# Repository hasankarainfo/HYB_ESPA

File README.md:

# HYB_ESPA CNC CONTROLLER BOARD
4 Adet Step motor bağlanabilir CNC kontrol kartı.

<p align="center"> Tasarım Ön Görünüm</p>

<p align="center"> Tasarım Arka Görünüm </p>

### ESP32 ile tasarlanmış cnc kontrolcü kartlarına genel bakış;

Temelde donanımsal olarak iki farklı yapıda görmek mümkün. 
İlki daha sade olan (ESPA), doğrudan mcu pinleri ile çevresel bileşen bağlantılandırılmış. 
İkincisi ise (ESPE), bazı bileşenlerin çıkış gpio ihtiyaçları için hc595 entegreleri kullanılıyor olması.

FYSETC_E4, Hem marlin hem fluidnc hem grbl firmware yazılımlarıyla uyumlu hemde açık kaynak paylaşılan projeden şematik olarak faydalanmak mümkün.
Altium ile geliştirilen proje açık kaynak paylaşılmıştır. 4 Adet TMC2209 dahili olarak step sürücüleri üzerinde barındırıyor. 
Sürücü uart bağlantıları ve uart donanımsal adreslemesini kullanmaktadır.

MKS-TinyBee, firmware yazılımları ile yine fazlaca uyumlu, yalnız kaynak tasarım olarak açık da yalnızca pdf bulunuyor. GPIO genişleme yapısı kullanılıyor. 
5 adet motor sürücü için 2* dip-8 header standart pololu breakout yapısı kullanılarak esnek motor sürücü bağlantı seçeneği sunmakta. 
yalnız TMC2208 ve ..09 için uart bağlantısı göz ardı edilmiş. Step sürücü header pinlerindeki RST ve SLP pinleri doğrudan kısa devre edili olmaktadır.

MRR_ESPE kicad ile tasarlanmış ve açık kaynak olarak paylaşılmış, tinybee ile yapısal olarak ve mcu pin görevleri olarak fazlaca benzerliği bulunan bir proje.
ek olarak SPI uyumlu step sürücüler ile haberleşmeli kullanılabilmesi için jumper seçenekleri sunmakta. 

Step sürücü header pinlerindeki MS1, MS2, MS3, RST jumper ile kontrol edilebilirken RST ve SLP pinleri de hem jumper ile kısa devre yapılaibliyor hemde kısa devre kaldırılıp mcu ya bağlanabiliyor. Özellikle TMC2208 ve ..09 uart haberleşmesi için MS3->TX ve SLP->RX olarak kullanılabileceği için gerekli esneklikler sağlanmış olmakta. 

MRR_ESPA ise yine açık kaynak paylaşılmış gpio genişleme kullanılmayan versiyonu olarak düşünülebilir.

Uart haberleşmeli step motor sürücüleri, çoğu kontrolcüye etkili düzeyde avantaj sağlamaktadır. 
Her sürücü Uart haberleşmesi için ayrıca mcu ya bağlamak fazlaca gpio kullanımı gerektirebilir.
ESP32 nin kısıtlı pin durumu için bu bir problem haline gelir. Bu sebeple Tek bir sürücüyü hem rx hem tx ile mcu bağlayıp, tüm sürücülerin sadece rx pinlerini paralel bağlamak kısmen çözüm olabiliyor.

Toplamda 2 pin gpio kullanılarak tüm sürücülere komut gönderimi mümkün olabiliyor, özellikle mod geçişleri, eşik değerleri, akım limiti microstep gibi değerlerin güncellenmesi mümkün olur.
TMC2209 uart adresleme özelliği bulunur iken TMC2208 bu özelliği desteklemez ve adres farketmeksizin tüm komutlara geri bildirim göndermektedir.
TMC2209 step motor limit switch özelliği barındırır, TMC2208 bu özellik yine bulunmamaktadır.
TMC2209 Uart adreslemesi için MS1 ve MS2 pinlerini kullanır, farklı adreslenerek uart bağlantısı paralellenmiş TMC2209 sürücüleri ile birebir haberleşme mümkün olur. 

Tek uart bağlantısı ile çoklu TMC2208 haberleşmesi kısmen mümkün olabilmektedir. Sürücülerin hepsi rx özelliği aktif iken, yalnızca birisi tx yapabilecek donanım yapısı kurgulandığında tüm sürücülere aynı parametre yükleme başarılı olmaktadır.

Açık kaynak paylaşımlar incelendiğinde esnek ve sade yapısı ile FYSETC_E4 projesi dikkat çekmektedir. 

Kendi tasarımımızı şekillendirirken özellikle gpio numara görev atamalarında ve step motor sürücü sayısında FYSETC_E4 esinlenmiş olduk.

### Tasarıma ilişkin;
1. Step motor sürücüleri pololu breakout pin yapısına uyumlu tasarlanarak, farklı step motor sürücülerine uyumluluk sağlandı. 
2. TMC2208 sürücüleri ile kullanıldığında uart üzerinden parametre yüklenebilir iken, TMC2209 ile UART RX-TX jumper takılarak, ve sürücülerde MS1, MS2 jumper configurasyonu ile uart adreslemeli kullanılabilirlik sağlandı.
3. +24V giriş voltajı ve P-mos yapısında ters bağlantı koruma özelliği eklendi.
4. Air out çıkışı ile, 42A akım değerinde ki P-mos ile Denetleyiciden kontrol edilen güçlü bir çıkış elde edildi. 24V ile beslenen lazer yada spindle doğrudan bu terminalden beslenebilir.
5. Emergency Switch terminal ile, step motor beslemesi ve Air out çıkışı, kontrolcüden bağımsız olarak kesilebilir. Kontrolcü beslemesi ve 5V hattı enerjisi aktif devam eder.
6. 5V fan çıkışı, USB ve LimitSwitch enerji hatları bağımsız PTC sigortaları ile akım korumaları eklendi.
7. Limit switch girişleri x,y ve z eksenleri için çiftlendi, aynı eksene iki farklı limit switch eklenebilir. Limit switch bağlantısı koparsa algılayabilir. Kullanılmayan giriş gnd jumper bağlanmalıdır.
8. Boot için kullanılan gpio 0 Probe bağlantısı için de kullanılmaya başlandı. ESP32 e kod atmak için Probe pini 5v jumperda iken kart resetlenerek başlatılmalıdır.
9. Tasarım aracı olarak Kicad 9 kullanıldı.

###  Layout tarafında;
1. Arduino mega2560 fiziksel boyutlarından esinlenerek 60x100 mm^2 ile alternatif cnc kontrolcü kartlarına kıyasla daha küçük ve sade yapıda tasarlandı.
2. Çift yüz tasarım yapılırken, yalnız 0.8mm delikli vialar kullanıldı. THT komponentler yalnızca arka katmandan bağlantılandı. 
3. Komponentlerin altında via bırakılmayarak kendin yap pcb üretim teknikleri ile üretim mümkün kılındı.
4. 40x40 fan doğrudan pcb üzerine distanslar ile sabitlenebilecek şekilde M3 vida delikleri yerleştirildi.

### ÜRETİM
Profesyonel pcb üretimi için; Plot klasörü içerisinde gerber ve drill dosyaları oluşturuldu.

Kendin yap seçeneği ile pcb üretimi için;
1. Plot_DIY klasörü içerisinde pcb delim için 0.8, 0.9, 1.2, 1.4, 3 mm kalınlıklarında matkap uçlarında farklı gcode lar oluşturuldu.
2. PCB komponent lehimleme işlemi için, F_Paste lazer kesim dosyası ayrıca oluşturuldu. Standart etiket kağıdına kesim yapılabilmektedir.
3. Ön yüz ve Arka yüz lazer kazıma ve hizalaması için gerekli dosyalar oluşturuldu.
4. ESP32 montajlanırken kullanılmayan pinler kapton bant ile izolasyon sağlanmalıdır.
5. ibom klasörü içerisinde html uzantılı web browser da görüntülemek üzere bom dosyası oluşturuldu. Komponent yerleşim ve dizgisinde kullanılabilmektedir.
6. Tüm lazer cnc üretim dosyaları 30W optik gücünde ki lazer makinasına göre kurgulanmıştır. Güç oranlaması ile farklı güçte ki lazer makinalarına uygunlaştırılabilir.

### 0.1b versiyon kendin yap teknikleri ile üretilmiş prototiplere ilişkin görseller

<p align="center">SMD Dizgili Ön ve Arka Görünüm </p>

<p align="center">Tam Dizgili ve Makine Montajlanmış Görünüm </p>

İlk prototipleme ile birlikte küçük çaplı düzeltmeler tasarımda ve üretim dosyalarında güncellenmiş (v0.1) haldedir.

Bom list oluşturulurken Türkiye piyasasından temin edilmek üzere ürün linkleri oluşturuldu. Yalnız CH340E IC yerli piyasada bulunamadı. 
Belirtilen fiyat bilgileri için ise, vergiler dahil edildi, güncel dolar kuru esas alındı ve dolara çevrildi.

### Bazı testlere ilişkin;
1. Firmware olarak fluidnc v3.9.4 yüklendi. Kontrolcüyle uyumlu, oluşturulan config.yaml dosyası "Settings/" dizini içerisine yerleştirildi.
2. X, Y ve Z eksenleri için 3 adet TMC2208 step motor sürücüleri bağlandı. Tüm sürücülere parametre yükleme yapılabildiği teyit edildi.
3. Arayüz olarak UGS (version 2.1.12) ile bağlanarak temel testler başarıyla sağlandı. 
4. Fiziksel SD kart takılarak web arayüz üzerinden .gcode yüklendi ve ilgili gcode çalıştırıldı. 
5. AirOut çıkışına fiziksel röle bağlandı ve röle çıkışına spindle 220V beslemesi bağlandı.
6. Fluidnc config ayarlarında AirOut çıkışı pwm enable pini ile ilişkilendirildi. 
7. M3 komutu çalıştırılarak Spindle enerjisi sağlandı, M5 komutu çalıştırıldığında Spindle enerjisi otomatik kesildi.
8. Pwm çıkışı ile spindle motor hız ayarı çalıştırıldı.
9. Kontrolcü spindle için enerji çıkışı sağlarken de acil stop basıldığında, spindle enerjisi doğrudan kesilebildi.
10. Limit switch kablo temassızlığı algılanabildiği görüldü.

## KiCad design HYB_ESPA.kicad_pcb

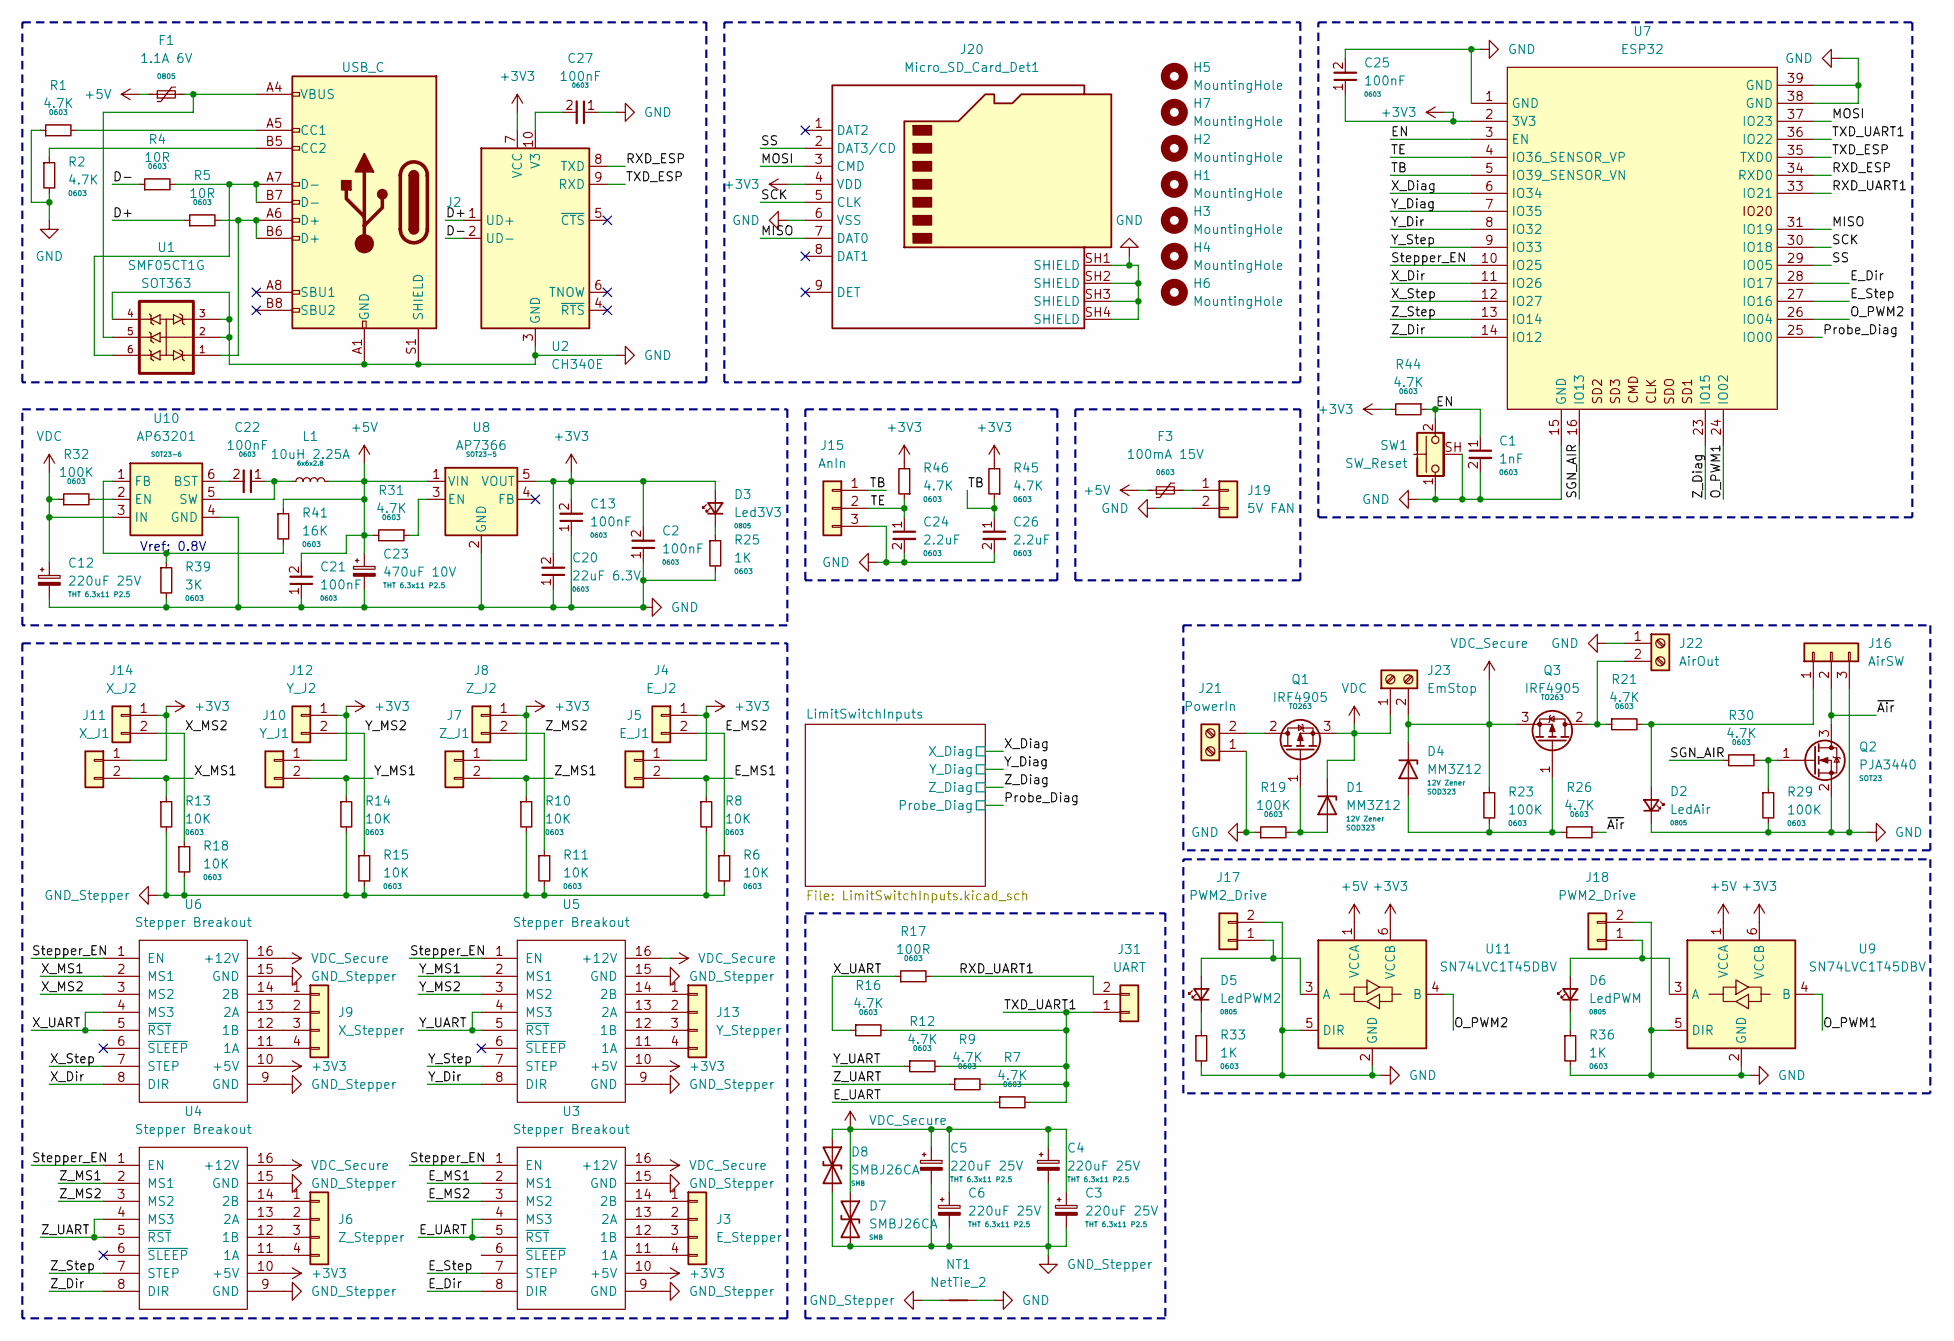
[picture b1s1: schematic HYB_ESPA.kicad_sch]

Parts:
C1: 1nF; C_0603_1608Metric; Part Number CL10B102KB8NNNC
C2, C13, C21, C22, C25, C27: 100nF; C_0603_1608Metric_SlimPad; Part Number CC0603KRX7R9BB104
C3, C4, C5, C6, C12: 220uF 25V; CP_Radial_D6.3mm_H11.0mm_P2.50mm; Part Number TMP221M1EE11M
C20: 22uF 6.3V; C_0603_1608Metric; Part Number CL10A226MQ8NRNC
C23: 470uF 10V; CP_Radial_D6.3mm_H11.0mm_P2.50mm; Part Number PKLH-010V471ME110-T2.5
C24, C26: 2.2uF; C_0603_1608Metric_SlimPad; Part Number CL10A225KQ8NNNC
D1, D4: MM3Z12; D_SOD-323_HandSoldering; Part Number MM3Z12-HT
D2: LedAir; LED_0805_2012Metric-s; Part Number HL-PSC-2012H233W-HF4
D3: Led3V3; LED_0805_2012Metric-s; Part Number HL-PSC-2012H233W-HF4
D5: LedPWM2; LED_0805_2012Metric-s; Part Number HL-PSC-2012H233W-HF4
D6: LedPWM; LED_0805_2012Metric-s; Part Number HL-PSC-2012H233W-HF4
D7, D8: SMBJ26CA; D_SMB_SmallPad; Part Number SMBJ26CA-HT
F1: 1.1A 6V; Fuse_0805_2012Metric; Part Number KLM2S110RY
F3: 100mA 15V; Fuse_0603_1608Metric; Part Number FSMD010-0603-R
H1, H2, H3, H4, H5, H6, H7: MountingHole; MountingHole_3.2mm_M3_DIN965_SmallPad
J2: USB_C; USB_C_Receptacle_GCT_USB4105-xx-A_16P_TopMnt_Horizontal_SPEC; Part Number nc
J3: E_Stepper; JST_XH_B4B-XH-A_1x04_P2.50mm_Vertical; Part Number DS1069-4MVW6X
J4: E_J2; PinHeader_1x02_P2.54mm_Vertical_1L; Part Number DS1069-2MVW6X
J5: E_J1; PinHeader_1x02_P2.54mm_Vertical_1L; Part Number DS1069-2MVW6X
J6: Z_Stepper; JST_XH_B4B-XH-A_1x04_P2.50mm_Vertical; Part Number DS1069-4MVW6X
J7: Z_J1; PinHeader_1x02_P2.54mm_Vertical_1L; Part Number DS1069-2MVW6X
J8: Z_J2; PinHeader_1x02_P2.54mm_Vertical_1L; Part Number DS1069-2MVW6X
J9: X_Stepper; JST_XH_B4B-XH-A_1x04_P2.50mm_Vertical; Part Number DS1069-4MVW6X
J10: Y_J1; PinHeader_1x02_P2.54mm_Vertical_1L; Part Number DS1069-2MVW6X
J11: X_J1; PinHeader_1x02_P2.54mm_Vertical_1L; Part Number DS1069-2MVW6X
J12: Y_J2; PinHeader_1x02_P2.54mm_Vertical_1L; Part Number DS1069-2MVW6X
J13: Y_Stepper; JST_XH_B4B-XH-A_1x04_P2.50mm_Vertical; Part Number DS1069-4MVW6X
J14: X_J2; PinHeader_1x02_P2.54mm_Vertical_1L; Part Number DS1069-2MVW6X
J15: AnIn; JST_XH_B3B-XH-A_1x03_P2.50mm_Vertical; Part Number L-KLS1-2.50-03-S
J16: AirSW; JST_XH_B3B-XH-A_1x03_P2.50mm_Vertical; Part Number L-KLS1-2.50-03-S
J17, J18: PWM2_Drive; JST_XH_B2B-XH-A_1x02_P2.50mm_Vertical; Part Number DS1069-2MVW6X
J19: 5V FAN; JST_XH_B2B-XH-A_1x02_P2.50mm_Vertical; Part Number DS1069-2MVW6X
J20: Micro_SD_Card_Det1; MicroSD_Card_Holder; Part Number 112I-TA01
J21: PowerIn; PhoenixContact_MSTBVA_2,5_2-G-5,08_1x02_P5.08mm_Vertical; Part Number ZB2EDGV-5.08-2P
J22: AirOut; TerminalBlock_Phoenix_PT-1,5-2-3.5-H_1x02_P3.50mm_Horizontal; Part Number 15EDGVC-3.5-02P-12-00AH
J23: EmStop; PhoenixContact_MSTBVA_2,5_2-G-5,08_1x02_P5.08mm_Vertical; Part Number ZB2EDGV-5.08-2P
J31: UART; PinHeader_1x02_P2.54mm_Vertical_1L; Part Number DS1069-2MVW6X
L1: 10uH 2.25A; L_CoreMaster_NR6028; Part Number NR6028-100M
NT1: NetTie_2; NetTie-2_SMD_Pad2.0mm
Q1, Q3: IRF4905; TO-263-2-S; Part Number IRF4905STRLPBF
Q2: PJA3440; SOT-23-3-s; Part Number PJA3440_R2_00001
R1, R2, R7, R9, R12, R16, R21, R26, R30, R31, R44, R45, R46: 4.7K; R_0603_1608Metric; Part Number RC0603FR-074K7L
R4, R5: 10R; R_0603_1608Metric; Part Number CQ03SAF100JT5E
R6, R8, R10, R11, R13, R14, R15, R18: 10K; R_0603_1608Metric; Part Number 0603SAF1002T5E
R17: 100R; R_0603_1608Metric; Part Number 0603SAF1000T5E
R19, R23, R29, R32: 100K; R_0603_1608Metric; Part Number 0603SAF1003T5E
R25, R33, R36: 1K; R_0603_1608Metric; Part Number 0603SAF1001T5E
R39: 3K; R_0603_1608Metric; Part Number 0603SAF3001T5E
R41: 16K; R_0603_1608Metric; Part Number 0603SAF1602T5E
SW1: SW_Reset; SW_Tactile_SPST_Angled_PTS645Vx39-2LFS_Shielded; Part Number L-KLS7-TS6606-5.0-180
U1: SMF05CT1G; TSOT-23-6_SlimPad; Part Number SMF05CT1G
U2: CH340E; MSOP-10_3x3mm_P0.5mm_SlimPad; Part Number C99652
U3, U4, U5, U6: Stepper Breakout; Pololu_Breakout-16_15.2x20.3mm_TMC; Part Number MSK.STP.01.000018
U7: ESP32; ESP32_WROOM_SIMPLE; Part Number ESP32-WROOM-32UE-N4.ESP
U8: AP7366; TSOT-23-5; Part Number AP7366EA-33W5-7
U9, U11: SN74LVC1T45DBV; SOT-23-6; Part Number SN74LVC1T45DBVT
U10: AP63201; TSOT-23-6_SlimPad; Part Number AP63201WU-7

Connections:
+3V3: C2.2, C13.2, C20.2, C25.1, D3.2 (A), J4.1, J5.1, J7.1, J8.1, J10.1, J11.1, J12.1, J14.1, J20.4 (VDD), R44.2, R45.2, R46.2, U2.7 (VCC), U3.10 (+5V), U4.10 (+5V), U5.10 (+5V), U6.10 (+5V), U7.2 (3V3), U8.5 (VOUT), U9.6 (VCCB), U11.6 (VCCB); also elsewhere on the board
+5V: C21.2, C23.1, F1.1, F3.1, L1.1, R31.2, R41.1, U8.1 (VIN), U9.1 (VCCA), U11.1 (VCCA); also elsewhere on the board
/D+: R5.1, U2.1 (UD+)
/D-: R4.1, U2.2 (UD-)
/EN: C1.1, R44.1, SW1.2, U7.3 (EN)
/E_Dir: U3.8 (DIR), U7.28 (IO17)
/E_MS1: J5.2, R8.1, U3.2 (MS1)
/E_MS2: J4.2, R6.1, U3.3 (MS2)
/E_Step: U3.7 (STEP), U7.27 (IO16)
/E_UART: R7.1, U3.4 (MS3), U3.5 (~RST)
/MISO: J20.7 (DAT0), U7.31 (IO19)
/MOSI: J20.3 (CMD), U7.37 (IO23)
/O_PWM1: U7.24 (IO02), U9.4 (B)
/O_PWM2: U7.26 (IO04), U11.4 (B)
/Probe_Diag: U7.25 (IO00); also elsewhere on the board
/RXD_ESP: U2.8 (TXD), U7.34 (RXD0)
/RXD_UART1: J31.2, R17.2, U7.33 (IO21)
/SCK: J20.5 (CLK), U7.30 (IO18)
/SGN_AIR: R30.2, U7.16 (IO13)
/SS: J20.2 (DAT3/CD), U7.29 (IO05)
/Stepper_EN: U3.1 (EN), U4.1 (EN), U5.1 (EN), U6.1 (EN), U7.10 (IO25)
/TB: C26.1, J15.1, R45.1, U7.5 (IO39_SENSOR_VN)
/TE: C24.1, J15.2, R46.1, U7.4 (IO36_SENSOR_VP)
/TXD_ESP: U2.9 (RXD), U7.35 (TXD0)
/TXD_UART1: J31.1, R7.2, R9.2, R12.2, R16.2, U7.36 (IO22)
/X_Diag: U7.6 (IO34); also elsewhere on the board
/X_Dir: U6.8 (DIR), U7.11 (IO26)
/X_MS1: J11.2, R13.1, U6.2 (MS1)
/X_MS2: J14.2, R18.1, U6.3 (MS2)
/X_Step: U6.7 (STEP), U7.12 (IO27)
/X_UART: R16.1, R17.1, U6.4 (MS3), U6.5 (~RST)
/Y_Diag: U7.7 (IO35); also elsewhere on the board
/Y_Dir: U5.8 (DIR), U7.8 (IO32)
/Y_MS1: J10.2, R14.1, U5.2 (MS1)
/Y_MS2: J12.2, R15.1, U5.3 (MS2)
/Y_Step: U5.7 (STEP), U7.9 (IO33)
/Y_UART: R12.1, U5.4 (MS3), U5.5 (~RST)
/Z_Diag: U7.23 (IO15); also elsewhere on the board
/Z_Dir: U4.8 (DIR), U7.14 (IO12)
/Z_MS1: J7.2, R10.1, U4.2 (MS1)
/Z_MS2: J8.2, R11.1, U4.3 (MS2)
/Z_Step: U4.7 (STEP), U7.13 (IO14)
/Z_UART: R9.1, U4.4 (MS3), U4.5 (~RST)
/~Air: J16.2, Q2.3 (D), R26.1
GND: C1.2, C2.1, C12.2, C13.1, C20.1, C21.1, C23.2, C24.2, C25.2, C26.2, C27.1, D2.1 (K), J2.A1 (GND), J2.A12 (GND), J2.B1 (GND), J2.B12 (GND), J2.S1 (SHIELD), J15.3, J16.3, J17.2, J18.2, J19.2, J20.6 (VSS), J20.SH1 (SHIELD), J20.SH2 (SHIELD), J20.SH3 (SHIELD), J20.SH4 (SHIELD), J21.1, J22.1, NT1.2, Q2.2 (S), R1.1, R2.2, R19.1, R25.2, R29.2, R33.2, R36.2, R39.2, SW1.1, SW1.SH (B), U1.2, U1.3, U1.4, U2.3 (GND), U7.1 (GND), U7.15 (GND), U7.38 (GND), U7.39 (GND), U8.2 (GND), U9.2 (GND), U9.5 (DIR), U10.4 (GND), U11.2 (GND), U11.5 (DIR); also elsewhere on the board
GND_Stepper: C3.2, C4.2, C5.2, C6.2, D7.2 (A2), D8.2 (A2), NT1.1, R6.2, R8.2, R10.2, R11.2, R13.2, R14.2, R15.2, R18.2, U3.9 (GND), U3.15 (GND), U4.9 (GND), U4.15 (GND), U5.9 (GND), U5.15 (GND), U6.9 (GND), U6.15 (GND)
unnamed: D1.2 (A), Q1.1 (G), R19.2
unnamed: D2.2 (A), J16.1, R21.2
unnamed: D3.1 (K), R25.1
unnamed: D4.2 (A), Q3.1 (G), R23.2, R26.2
unnamed: D5.2 (A), J17.1, U11.3 (A)
unnamed: D5.1 (K), R33.1
unnamed: D6.2 (A), J18.1, U9.3 (A)
unnamed: D6.1 (K), R36.1
unnamed: F1.2, J2.A4 (VBUS), J2.A9 (VBUS), J2.B4 (VBUS), J2.B9 (VBUS), U1.5
unnamed: J2.A5 (CC1), R1.2
unnamed: J2.B5 (CC2), R2.1
unnamed: J2.A6 (D+), J2.B6 (D+), R5.2, U1.1
unnamed: J2.A7 (D-), J2.B7 (D-), R4.2, U1.6
unnamed: J3.1, U3.14 (2B)
unnamed: J3.2, U3.13 (2A)
unnamed: J3.3, U3.12 (1B)
unnamed: J3.4, U3.11 (1A)
unnamed: J6.1, U4.14 (2B)
unnamed: J6.2, U4.13 (2A)
unnamed: J6.3, U4.12 (1B)
unnamed: J6.4, U4.11 (1A)
unnamed: J9.1, U6.14 (2B)
unnamed: J9.2, U6.13 (2A)
unnamed: J9.3, U6.12 (1B)
unnamed: J9.4, U6.11 (1A)
unnamed: J13.1, U5.14 (2B)
unnamed: J13.2, U5.13 (2A)
unnamed: J13.3, U5.12 (1B)
unnamed: J13.4, U5.11 (1A)
unnamed: F3.2, J19.1
unnamed: J21.2, Q1.2 (S)
unnamed: J22.2, Q3.2 (S), R21.1
unnamed: Q2.1 (G), R29.1, R30.1
unnamed: C27.2, U2.10 (V3)
unnamed: R31.1, U8.3 (EN)
unnamed: C22.2, U10.6 (BST)
unnamed: R32.2, U10.2 (EN)
unnamed: R39.1, R41.2, U10.1 (FB)
unnamed: C22.1, L1.2, U10.5 (SW)
VDC: C12.1, D1.1 (K), J23.1, Q1.3 (D), R32.1, U10.3 (IN)
VDC_Secure: C3.1, C4.1, C5.1, C6.1, D4.1 (K), D7.1 (A1), D8.1 (A1), J23.2, Q3.3 (D), R23.1, U3.16 (+12V), U4.16 (+12V), U5.16 (+12V), U6.16 (+12V)

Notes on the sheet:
Vref: 0.8V

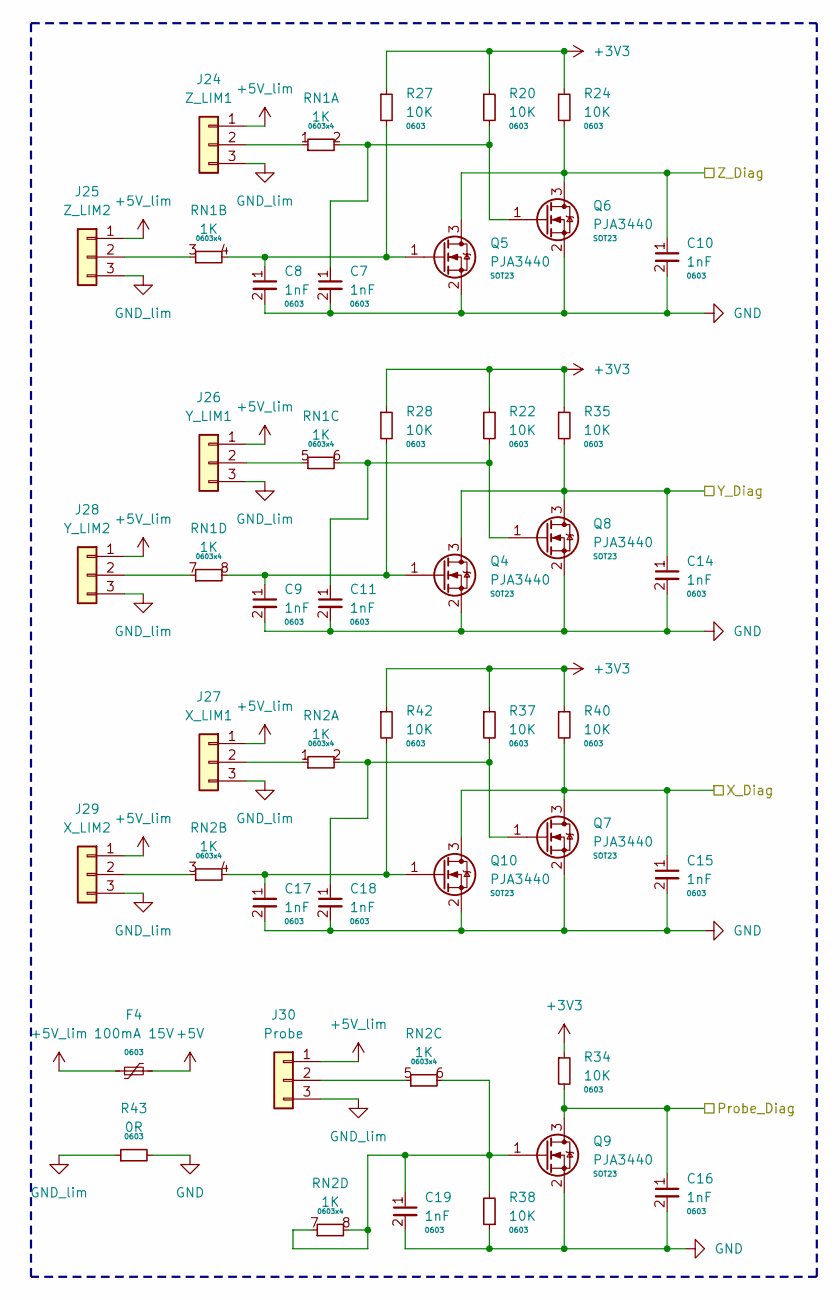
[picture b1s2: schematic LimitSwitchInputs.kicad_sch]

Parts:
C7, C8, C9, C10, C11, C14, C15, C16, C17, C18, C19: 1nF; C_0603_1608Metric; Part Number CL10B102KB8NNNC
F4: 100mA 15V; Fuse_0603_1608Metric; Part Number FSMD010-0603-R
J24: Z_LIM1; JST_XH_B3B-XH-A_1x03_P2.50mm_Vertical; Part Number L-KLS1-2.50-03-S
J25: Z_LIM2; JST_XH_B3B-XH-A_1x03_P2.50mm_Vertical; Part Number L-KLS1-2.50-03-S
J26: Y_LIM1; JST_XH_B3B-XH-A_1x03_P2.50mm_Vertical; Part Number L-KLS1-2.50-03-S
J27: X_LIM1; JST_XH_B3B-XH-A_1x03_P2.50mm_Vertical; Part Number L-KLS1-2.50-03-S
J28: Y_LIM2; JST_XH_B3B-XH-A_1x03_P2.50mm_Vertical; Part Number L-KLS1-2.50-03-S
J29: X_LIM2; JST_XH_B3B-XH-A_1x03_P2.50mm_Vertical; Part Number L-KLS1-2.50-03-S
J30: Probe; JST_XH_B3B-XH-A_1x03_P2.50mm_Vertical; Part Number L-KLS1-2.50-03-S
Q4, Q5, Q6, Q7, Q8, Q9, Q10: PJA3440; SOT-23-3-s; Part Number PJA3440_R2_00001
R20, R22, R24, R27, R28, R34, R35, R37, R38, R40, R42: 10K; R_0603_1608Metric; Part Number 0603SAF1002T5E
R43: 0R; R_0603_1608Metric; Part Number 0603SAF0000T5E
RN1, RN2: 1K; R_Array_Convex_4x0603-s; Part Number 4D03WGF1001T5E

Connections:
+3V3: R20.1, R22.1, R24.1, R27.1, R28.1, R34.1, R35.1, R37.1, R40.1, R42.1; also elsewhere on the board
+5V: F4.2; also elsewhere on the board
+5V_lim: F4.1, J24.1, J25.1, J26.1, J27.1, J28.1, J29.1, J30.1
/Probe_Diag: C16.1, Q9.3 (D), R34.2; also elsewhere on the board
/X_Diag: C15.1, Q7.3 (D), Q10.3 (D), R40.2; also elsewhere on the board
/Y_Diag: C14.1, Q4.3 (D), Q8.3 (D), R35.2; also elsewhere on the board
/Z_Diag: C10.1, Q5.3 (D), Q6.3 (D), R24.2; also elsewhere on the board
GND: C7.2, C8.2, C9.2, C10.2, C11.2, C14.2, C15.2, C16.2, C17.2, C18.2, C19.2, Q4.2 (S), Q5.2 (S), Q6.2 (S), Q7.2 (S), Q8.2 (S), Q9.2 (S), Q10.2 (S), R38.1, R43.2; also elsewhere on the board
GND_lim: J24.3, J25.3, J26.3, J27.3, J28.3, J29.3, J30.3, R43.1
unnamed: J24.2, RN1.1
unnamed: J25.2, RN1.3
unnamed: J26.2, RN1.5
unnamed: J27.2, RN2.1
unnamed: J28.2, RN1.7
unnamed: J29.2, RN2.3
unnamed: J30.2, RN2.5
unnamed: C9.1, Q4.1 (G), R28.2, RN1.8
unnamed: C8.1, Q5.1 (G), R27.2, RN1.4
unnamed: C7.1, Q6.1 (G), R20.2, RN1.2
unnamed: C18.1, Q7.1 (G), R37.2, RN2.2
unnamed: C11.1, Q8.1 (G), R22.2, RN1.6
unnamed: C19.1, Q9.1 (G), R38.2, RN2.6, RN2.7, RN2.8
unnamed: C17.1, Q10.1 (G), R42.2, RN2.4

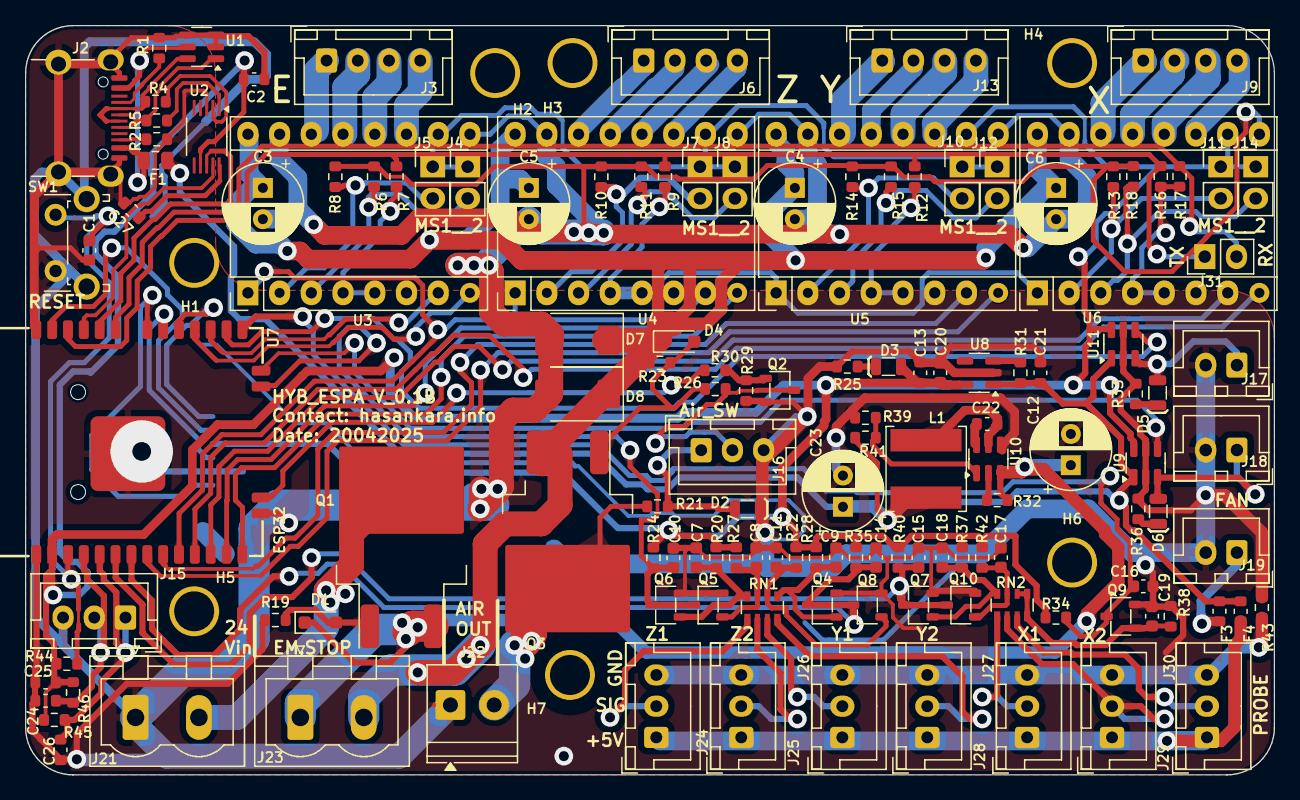
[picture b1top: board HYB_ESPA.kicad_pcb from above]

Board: 2 copper layers, 100.0 x 60.0 mm, 146 parts (1 on the bottom side), 103 nets.

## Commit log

2025-05-12 Fixed component name positions in, Top silk, F. Fab, and ibom, files.
2025-05-12 Updated Pwm speed map in Settings dir config.yaml file.
